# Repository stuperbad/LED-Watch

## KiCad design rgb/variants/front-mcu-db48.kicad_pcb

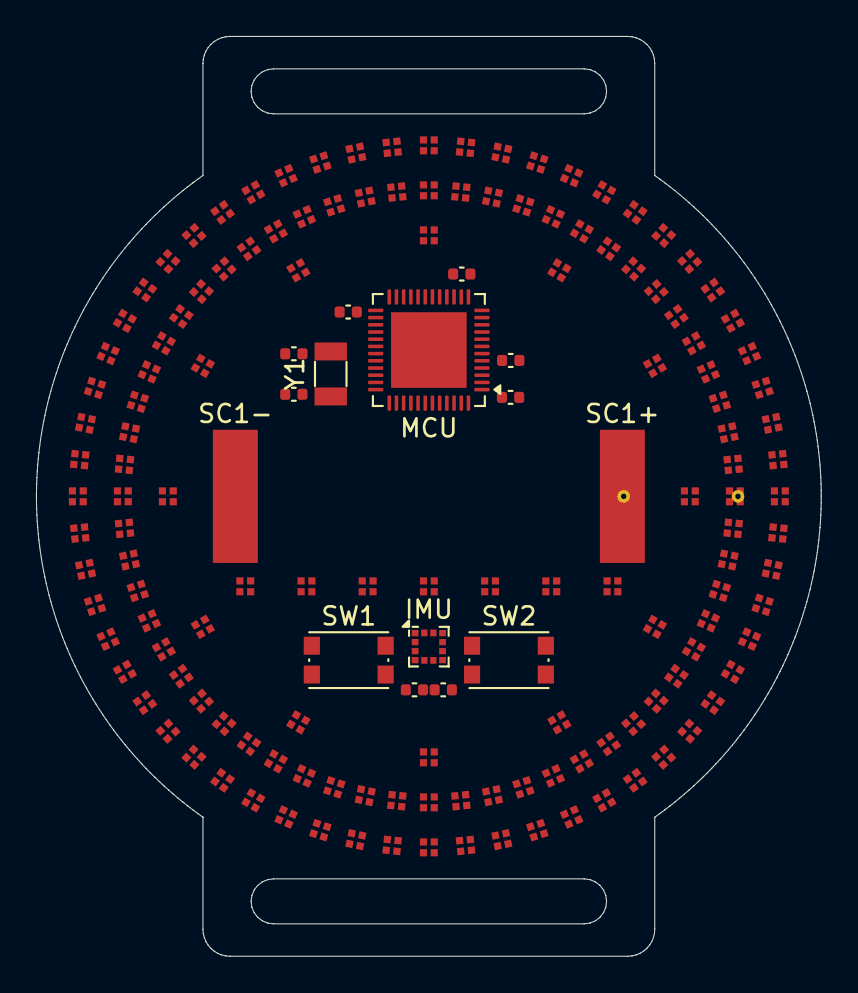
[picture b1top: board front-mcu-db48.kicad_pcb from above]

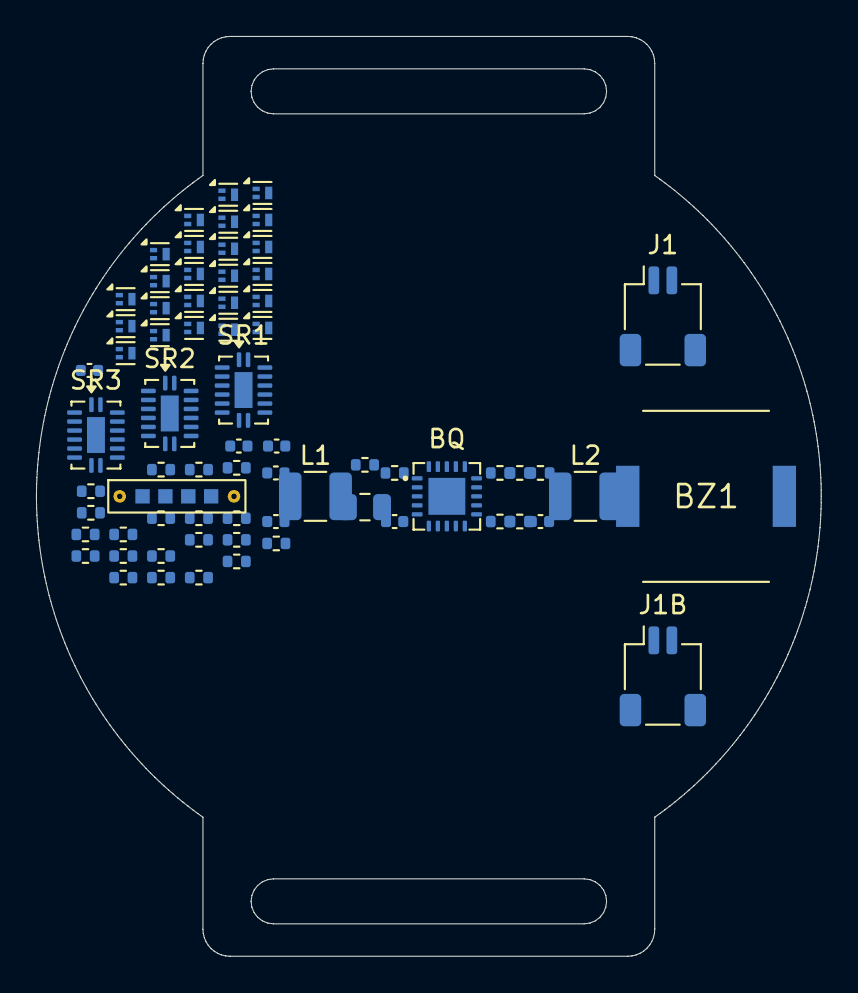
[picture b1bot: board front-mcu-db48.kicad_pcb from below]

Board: 4 copper layers, 43.6 x 51.1 mm, 223 parts (69 on the bottom side), 40 nets, no tracks yet.

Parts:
BQ: BQ25570; BQ25570RGR_VQFN-20_3.5x3.5mm_P0.5mm_EP2.05mm
BZ1: PKMCS0909E4000-R1; Piezo_Murata_PKMCS0909E4000-R1_9x9mm
C10, C11, C12, C30, C31: 100n; C_0402_1005Metric
C13: 10u; C_0402_1005Metric
C20, C21: 18p; C_0402_1005Metric
C50, C52: 4u7; C_0402_1005Metric
C51, C53: 10n; C_0402_1005Metric
C54: 22u; C_0805_2012Metric
CS1, CS2, CS3: 100n; C_0402_1005Metric
IMU: LIS2DW12; LGA-12_2x2mm_P0.5mm
IND1, IND2, IND3, IND4, IND5, IND6, IND7: NCD0808RGB1 / MHPA0808RGBDT; RGB0808_CommonAnode
J1, J1B: LiPo; JST_SH_SM02B-SRSS-TB_1x02-1MP_P1.00mm_Horizontal
J2: UPDI pogo; UPDI_Pogo_1x4_P1.27mm_2Guide
L1: 22uH; L_1210_3225Metric
L2: 10uH; L_1210_3225Metric
MCU: AVR128DB48-I/6LX; QFN-48-1EP_6x6mm_P0.4mm_EP4.2x4.2mm
Q1, Q2, Q3, Q4, Q5, Q6, Q7, Q8, Q9, Q10, Q11, Q12, Q13, Q14, Q15, Q16, Q17, Q18, Q19, Q20, Q21, Q22, Q23, Q24: DMP21D0UFB4; Diodes_DFN1006-3
R20, R21: 10k; R_0402_1005Metric
R50, R53, R55: 6.49M; R_0402_1005Metric
R51: 5.11M; R_0402_1005Metric
R52: 1.47M; R_0402_1005Metric
R54, R56: 3.74M; R_0402_1005Metric
RC1, RC2, RC3, RC4, RC5, RC6, RC7, RC8, RC9, RC10, RC11, RC12, RC13, RC14, RC15, RC16, RC17, RC18: R; R_0402_1005Metric
SC1+, SC1-: cell pad; KXOB25_cell_pad_2.5x7.4mm
SR1, SR2, SR3: 74HC595BQ; DHVQFN-16-1EP_2.5x3.5mm_P0.5mm_EP1x2mm
SW1, SW2: SW; SW_Push_1P1T_NO_CK_KMR2
U2, U3, U4, U5, U6, U7, U8, U9, U10, U11, U12, U13, U14, U15, U16, U17, U18, U19, U20, U21, U22, U23, U24, U25, U26, U27, U28, U29, U30, U31, U32, U33, U34, U35, U36, U37, U38, U39, U40, U41, U42, U43, U44, U45, U46, U47, U48, U49, U50, U51, U52, U53, U54, U55, U56, U57, U58, U59, U60, U61, U62, U63, U64, U65, U66, U67, U68, U69, U70, U71, U72, U73, U74, U75, U76, U77, U78, U79, U80, U81, U82, U83, U84, U85, U86, U87, U88, U89, U90, U91, U92, U93, U94, U95, U96, U97, U98, U99, U100, U101, U102, U103, U104, U105, U106, U107, U108, U109, U110, U111, U112, U113, U114, U115, U116, U117, U118, U119, U120, U121, U122, U123, U124, U125, U126, U127, U128, U129, U130, U131, U132, U133: NCD0808RGB1 / MHPA0808RGBDT; RGB0808_CommonAnode
Y1: 32.768kHz; Crystal_SMD_3215-2Pin_3.2x1.5mm

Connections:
/B1: U2.4, U8.4, U14.4, U20.4, U26.4, U32.4, U38.4, U44.4, U50.4, U56.4, U62.4, U68.4, U74.4, U80.4, U86.4, U92.4, U98.4, U104.4, U110.4, U116.4, U122.4, U128.4
/B2: U3.4, U9.4, U15.4, U21.4, U27.4, U33.4, U39.4, U45.4, U51.4, U57.4, U63.4, U69.4, U75.4, U81.4, U87.4, U93.4, U99.4, U105.4, U111.4, U117.4, U123.4, U129.4
/B3: U4.4, U10.4, U16.4, U22.4, U28.4, U34.4, U40.4, U46.4, U52.4, U58.4, U64.4, U70.4, U76.4, U82.4, U88.4, U94.4, U100.4, U106.4, U112.4, U118.4, U124.4, U130.4
/B4: U5.4, U11.4, U17.4, U23.4, U29.4, U35.4, U41.4, U47.4, U53.4, U59.4, U65.4, U71.4, U77.4, U83.4, U89.4, U95.4, U101.4, U107.4, U113.4, U119.4, U125.4, U131.4
/B5: U6.4, U12.4, U18.4, U24.4, U30.4, U36.4, U42.4, U48.4, U54.4, U60.4, U66.4, U72.4, U78.4, U84.4, U90.4, U96.4, U102.4, U108.4, U114.4, U120.4, U126.4, U132.4
/B6: U7.4, U13.4, U19.4, U25.4, U31.4, U37.4, U43.4, U49.4, U55.4, U61.4, U67.4, U73.4, U79.4, U85.4, U91.4, U97.4, U103.4, U109.4, U115.4, U121.4, U127.4, U133.4
/G1: U2.3, U8.3, U14.3, U20.3, U26.3, U32.3, U38.3, U44.3, U50.3, U56.3, U62.3, U68.3, U74.3, U80.3, U86.3, U92.3, U98.3, U104.3, U110.3, U116.3, U122.3, U128.3
/G2: U3.3, U9.3, U15.3, U21.3, U27.3, U33.3, U39.3, U45.3, U51.3, U57.3, U63.3, U69.3, U75.3, U81.3, U87.3, U93.3, U99.3, U105.3, U111.3, U117.3, U123.3, U129.3
/G3: U4.3, U10.3, U16.3, U22.3, U28.3, U34.3, U40.3, U46.3, U52.3, U58.3, U64.3, U70.3, U76.3, U82.3, U88.3, U94.3, U100.3, U106.3, U112.3, U118.3, U124.3, U130.3
/G4: U5.3, U11.3, U17.3, U23.3, U29.3, U35.3, U41.3, U47.3, U53.3, U59.3, U65.3, U71.3, U77.3, U83.3, U89.3, U95.3, U101.3, U107.3, U113.3, U119.3, U125.3, U131.3
/G5: U6.3, U12.3, U18.3, U24.3, U30.3, U36.3, U42.3, U48.3, U54.3, U60.3, U66.3, U72.3, U78.3, U84.3, U90.3, U96.3, U102.3, U108.3, U114.3, U120.3, U126.3, U132.3
/G6: U7.3, U13.3, U19.3, U25.3, U31.3, U37.3, U43.3, U49.3, U55.3, U61.3, U67.3, U73.3, U79.3, U85.3, U91.3, U97.3, U103.3, U109.3, U115.3, U121.3, U127.3, U133.3
/Hour1: U2.1, U3.1, U4.1, U5.1, U6.1, U7.1
/Hour2: U8.1, U9.1, U10.1, U11.1, U12.1, U13.1
/Minute1: U14.1, U15.1, U16.1, U17.1, U18.1, U19.1
/Minute2: U20.1, U21.1, U22.1, U23.1, U24.1, U25.1
/Minute3: U26.1, U27.1, U28.1, U29.1, U30.1, U31.1
/Minute4: U32.1, U33.1, U34.1, U35.1, U36.1, U37.1
/Minute5: U38.1, U39.1, U40.1, U41.1, U42.1, U43.1
/Minute6: U44.1, U45.1, U46.1, U47.1, U48.1, U49.1
/Minute7: U50.1, U51.1, U52.1, U53.1, U54.1, U55.1
/Minute8: U56.1, U57.1, U58.1, U59.1, U60.1, U61.1
/Minute9: U62.1, U63.1, U64.1, U65.1, U66.1, U67.1
/Minute10: U68.1, U69.1, U70.1, U71.1, U72.1, U73.1
/R1: U2.2, U8.2, U14.2, U20.2, U26.2, U32.2, U38.2, U44.2, U50.2, U56.2, U62.2, U68.2, U74.2, U80.2, U86.2, U92.2, U98.2, U104.2, U110.2, U116.2, U122.2, U128.2
/R2: U3.2, U9.2, U15.2, U21.2, U27.2, U33.2, U39.2, U45.2, U51.2, U57.2, U63.2, U69.2, U75.2, U81.2, U87.2, U93.2, U99.2, U105.2, U111.2, U117.2, U123.2, U129.2
/R3: U4.2, U10.2, U16.2, U22.2, U28.2, U34.2, U40.2, U46.2, U52.2, U58.2, U64.2, U70.2, U76.2, U82.2, U88.2, U94.2, U100.2, U106.2, U112.2, U118.2, U124.2, U130.2
/R4: U5.2, U11.2, U17.2, U23.2, U29.2, U35.2, U41.2, U47.2, U53.2, U59.2, U65.2, U71.2, U77.2, U83.2, U89.2, U95.2, U101.2, U107.2, U113.2, U119.2, U125.2, U131.2
/R5: U6.2, U12.2, U18.2, U24.2, U30.2, U36.2, U42.2, U48.2, U54.2, U60.2, U66.2, U72.2, U78.2, U84.2, U90.2, U96.2, U102.2, U108.2, U114.2, U120.2, U126.2, U132.2
/R6: U7.2, U13.2, U19.2, U25.2, U31.2, U37.2, U43.2, U49.2, U55.2, U61.2, U67.2, U73.2, U79.2, U85.2, U91.2, U97.2, U103.2, U109.2, U115.2, U121.2, U127.2, U133.2
/Second1: U74.1, U75.1, U76.1, U77.1, U78.1, U79.1
/Second2: U80.1, U81.1, U82.1, U83.1, U84.1, U85.1
/Second3: U86.1, U87.1, U88.1, U89.1, U90.1, U91.1
/Second4: U92.1, U93.1, U94.1, U95.1, U96.1, U97.1
/Second5: U98.1, U99.1, U100.1, U101.1, U102.1, U103.1
/Second6: U104.1, U105.1, U106.1, U107.1, U108.1, U109.1
/Second7: U110.1, U111.1, U112.1, U113.1, U114.1, U115.1
/Second8: U116.1, U117.1, U118.1, U119.1, U120.1, U121.1
/Second9: U122.1, U123.1, U124.1, U125.1, U126.1, U127.1
/Second10: U128.1, U129.1, U130.1, U131.1, U132.1, U133.1

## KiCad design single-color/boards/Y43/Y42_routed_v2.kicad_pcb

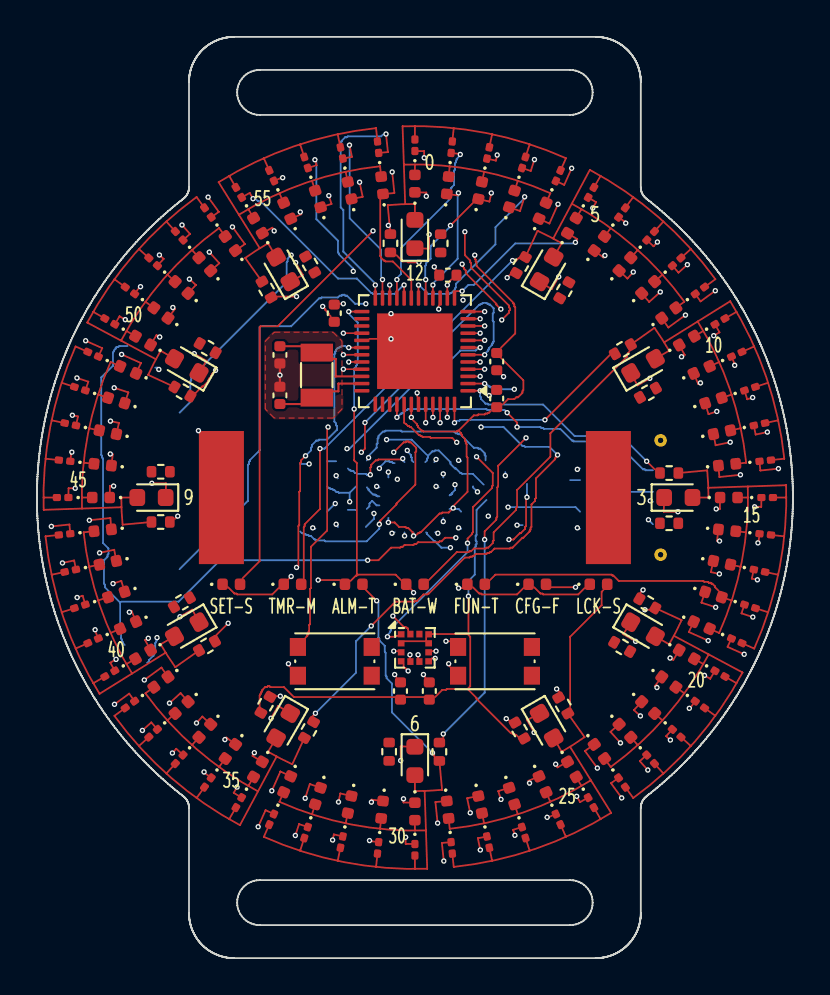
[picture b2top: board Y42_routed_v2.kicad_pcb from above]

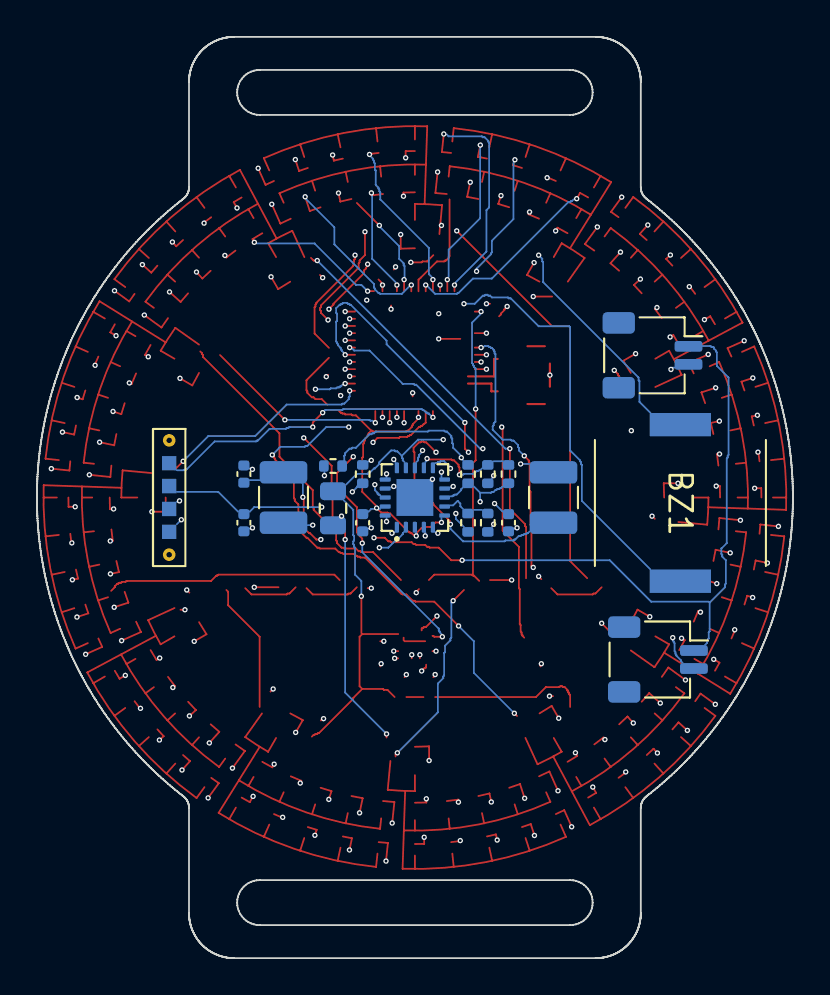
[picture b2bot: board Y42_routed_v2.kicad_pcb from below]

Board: 4 copper layers, 42.0 x 51.2 mm, 197 parts (19 on the bottom side), 61 nets.

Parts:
BZ1: PKMCS0909E4000-R1; Piezo_Murata_PKMCS0909E4000-R1_9x9mm
C10, C11, C12, C30, C31: 100n; C_0402_1005Metric
C13: 10u; C_0402_1005Metric
C20, C21: 18p; C_0402_1005Metric
C50, C52: 4u7; C_0402_1005Metric
C51, C53: 10n; C_0402_1005Metric
C54: 22u; C_0805_2012Metric
H1, H2, H3, H4, H5, H6, H7, H8, H9, H10, H11, H12: LED white 0603; LED_0603_1608Metric
IND1: SET; LED_0402_1005Metric
IND2: TMR; LED_0402_1005Metric
IND3: BAT; LED_0402_1005Metric
IND4: FUN; LED_0402_1005Metric
IND5: CFG; LED_0402_1005Metric
IND6, IND7: LCK; LED_0402_1005Metric
J1, J1B: LiPo; JST_SH_SM02B-SRSS-TB_1x02-1MP_P1.00mm_Horizontal
J2: UPDI pogo pads 1.27 mm (RESET VDD GND UPDI); UPDI_Pogo_1x4_P1.27mm_2Guide
L1: 22uH; L_1210_3225Metric
L2: 10uH; L_1210_3225Metric
M0, M1, M2, M3, M4, M5, M6, M7, M8, M9, M10, M11, M12, M13, M14, M15, M16, M17, M18, M19, M20, M21, M22, M23, M24, M25, M26, M27, M28, M29, M30, M31, M32, M33, M34, M35, M36, M37, M38, M39, M40, M41, M42, M43, M44, M45, M46, M47, M48, M49, M50, M51, M52, M53, M54, M55, M56, M57, M58, M59: LED white 0402; LED_0402_1005Metric
R1, R2, R3, R4, R5, R6, R7, R8, R9, R10, R11, R12: 220; R_0402_1005Metric
R20, R21, R57, R58, R59, R61, R62, R63, R64, R65, R66, R67: 10k; R_0402_1005Metric
R50, R53, R55: 6.49M; R_0402_1005Metric
R51: 5.11M; R_0402_1005Metric
R52: 1.47M; R_0402_1005Metric
R54, R56: 3.74M; R_0402_1005Metric
S0, S1, S2, S3, S4, S5, S6, S7, S8, S9, S10, S11, S12, S13, S14, S15, S16, S17, S18, S19, S20, S21, S22, S23, S24, S25, S26, S27, S28, S29, S30, S31, S32, S33, S34, S35, S36, S37, S38, S39, S40, S41, S42, S43, S44, S45, S46, S47, S48, S49, S50, S51, S52, S53, S54, S55, S56, S57, S58, S59: LED white 0201; LED_0201_0603Metric
SC1+, SC1-: cell pad; KXOB25_cell_pad_2.5x7.4mm
SW1, SW2: SW_Push; SW_Push_1P1T_NO_CK_KMR2
U1: AVR128DB48-I/6LX; QFN-48-1EP_6x6mm_P0.4mm_EP4.2x4.2mm
U2: LIS2DW12TR; LGA-12_2x2mm_P0.5mm
U4: BQ25570RGRR; BQ25570RGR_VQFN-20_3.5x3.5mm_P0.5mm_EP2.05mm
Y1: 32.768kHz; Crystal_SMD_3215-2Pin_3.2x1.5mm

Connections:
+3V3: C30.1, C31.1, C54.1, L2.2, R20.1, R21.1, U2.2, U2.9, U2.10, U4.14
/BATT: J1.1, J1B.1, U4.18
/BAT_OK: U1.33, U4.13
/BTN1: SW1.1, U1.31
/BTN2: SW2.1, U1.32
/BUZ_A: BZ1.1, U1.8
/BUZ_B: BZ1.2, U1.9
/COL0: H12.2, IND1.2, M0.2, M1.2, M2.2, M3.2, M4.2, R1.1, S0.2, S1.2, S2.2, S3.2, S4.2
/COL0_MCU: R1.2, U1.44
/COL1: H1.2, IND2.2, M5.2, M6.2, M7.2, M8.2, M9.2, R2.1, S5.2, S6.2, S7.2, S8.2, S9.2
/COL1_MCU: R2.2, U1.45
/COL2: H2.2, IND3.2, M10.2, M11.2, M12.2, M13.2, M14.2, R3.1, S10.2, S11.2, S12.2, S13.2, S14.2
/COL2_MCU: R3.2, U1.48
/COL3: H3.2, IND4.2, M15.2, M16.2, M17.2, M18.2, M19.2, R4.1, S15.2, S16.2, S17.2, S18.2, S19.2
/COL3_MCU: R4.2, U1.1
/COL4: H4.2, IND5.2, M20.2, M21.2, M22.2, M23.2, M24.2, R5.1, S20.2, S21.2, S22.2, S23.2, S24.2
/COL4_MCU: R5.2, U1.2
/COL5: H5.2, IND6.2, M25.2, M26.2, M27.2, M28.2, M29.2, R6.1, S25.2, S26.2, S27.2, S28.2, S29.2
/COL5_MCU: R6.2, U1.3
/COL6: H6.2, IND7.2, M30.2, M31.2, M32.2, M33.2, M34.2, R7.1, S30.2, S31.2, S32.2, S33.2, S34.2
/COL6_MCU: R7.2, U1.4
/COL7: H7.2, M35.2, M36.2, M37.2, M38.2, M39.2, R8.1, S35.2, S36.2, S37.2, S38.2, S39.2
/COL7_MCU: R8.2, U1.5
/COL8: H8.2, M40.2, M41.2, M42.2, M43.2, M44.2, R9.1, S40.2, S41.2, S42.2, S43.2, S44.2
/COL8_MCU: R9.2, U1.6
/COL9: H9.2, M45.2, M46.2, M47.2, M48.2, M49.2, R10.1, S45.2, S46.2, S47.2, S48.2, S49.2
/COL9_MCU: R10.2, U1.7
/COL10: H10.2, M50.2, M51.2, M52.2, M53.2, M54.2, R11.1, S50.2, S51.2, S52.2, S53.2, S54.2
/COL10_MCU: R11.2, U1.10
/COL11: H11.2, M55.2, M56.2, M57.2, M58.2, M59.2, R12.1, S55.2, S56.2, S57.2, S58.2, S59.2
/COL11_MCU: R12.2, U1.11
/IMU_INT: U1.30, U2.12
/LBOOST: L1.1, U4.20
/LBUCK: L2.1, U4.16
/OK_HYST: R52.2, R53.1, U4.10
/OK_PROG: R53.2, R54.1, U4.11
/RESET: J2.1, U1.40
/ROW0: H1.1, H2.1, H3.1, H4.1, H5.1, H6.1, H7.1, H8.1, H9.1, H10.1, H11.1, H12.1, U1.12
/ROW1: M0.1, M5.1, M10.1, M15.1, M20.1, M25.1, M30.1, M35.1, M40.1, M45.1, M50.1, M55.1, U1.13
/ROW2: M1.1, M6.1, M11.1, M16.1, M21.1, M26.1, M31.1, M36.1, M41.1, M46.1, M51.1, M56.1, U1.16
/ROW3: M2.1, M7.1, M12.1, M17.1, M22.1, M27.1, M32.1, M37.1, M42.1, M47.1, M52.1, M57.1, U1.17
/ROW4: M3.1, M8.1, M13.1, M18.1, M23.1, M28.1, M33.1, M38.1, M43.1, M48.1, M53.1, M58.1, U1.18
/ROW5: M4.1, M9.1, M14.1, M19.1, M24.1, M29.1, M34.1, M39.1, M44.1, M49.1, M54.1, M59.1, U1.19
/ROW6: S0.1, S5.1, S10.1, S15.1, S20.1, S25.1, S30.1, S35.1, S40.1, S45.1, S50.1, S55.1, U1.20
/ROW7: S1.1, S6.1, S11.1, S16.1, S21.1, S26.1, S31.1, S36.1, S41.1, S46.1, S51.1, S56.1, U1.21
/ROW8: S2.1, S7.1, S12.1, S17.1, S22.1, S27.1, S32.1, S37.1, S42.1, S47.1, S52.1, S57.1, U1.22
/ROW9: S3.1, S8.1, S13.1, S18.1, S23.1, S28.1, S33.1, S38.1, S43.1, S48.1, S53.1, S58.1, U1.23
/ROW10: S4.1, S9.1, S14.1, S19.1, S24.1, S29.1, S34.1, S39.1, S44.1, S49.1, S54.1, S59.1, U1.24
/ROW11: IND1.1, IND2.1, IND3.1, IND4.1, IND5.1, IND6.1, IND7.1, U1.25
/SCL: R21.2, U1.47, U2.1
/SDA: R20.2, U1.46, U2.4
/SOLAR_IN: C50.1, L1.2, U4.2
/UPDI: J2.4, U1.41
/VBAT_OV: R50.2, R51.1, U4.7
/VOUT_SET: R55.2, R56.1, U4.12
/VRDIV: R50.1, R52.1, R55.1, U4.8
/VREF_SAMP: C51.1, U4.4
/XTAL1: C20.1, U1.34, Y1.1
/XTAL2: C21.1, U1.35, Y1.2
GND: C10.2, C11.2, C12.2, C13.2, C20.2, C21.2, C30.2, C31.2, C50.2, C51.2, C52.2, C53.2, C54.2, J1.2, J1B.2, J2.3, R51.2, R54.2, R56.2, SC1-.1, SW1.2, SW2.2, U1.15, U1.29, U1.43, U1.49, U2.3, U2.5, U2.6, U2.7, U2.8, U4.1, U4.5, U4.9, U4.15, U4.17, U4.21
VBAT: C10.1, C11.1, C12.1, C13.1, C52.1, C53.1, J2.2, U1.14, U1.28, U1.42, U4.3, U4.6, U4.19
